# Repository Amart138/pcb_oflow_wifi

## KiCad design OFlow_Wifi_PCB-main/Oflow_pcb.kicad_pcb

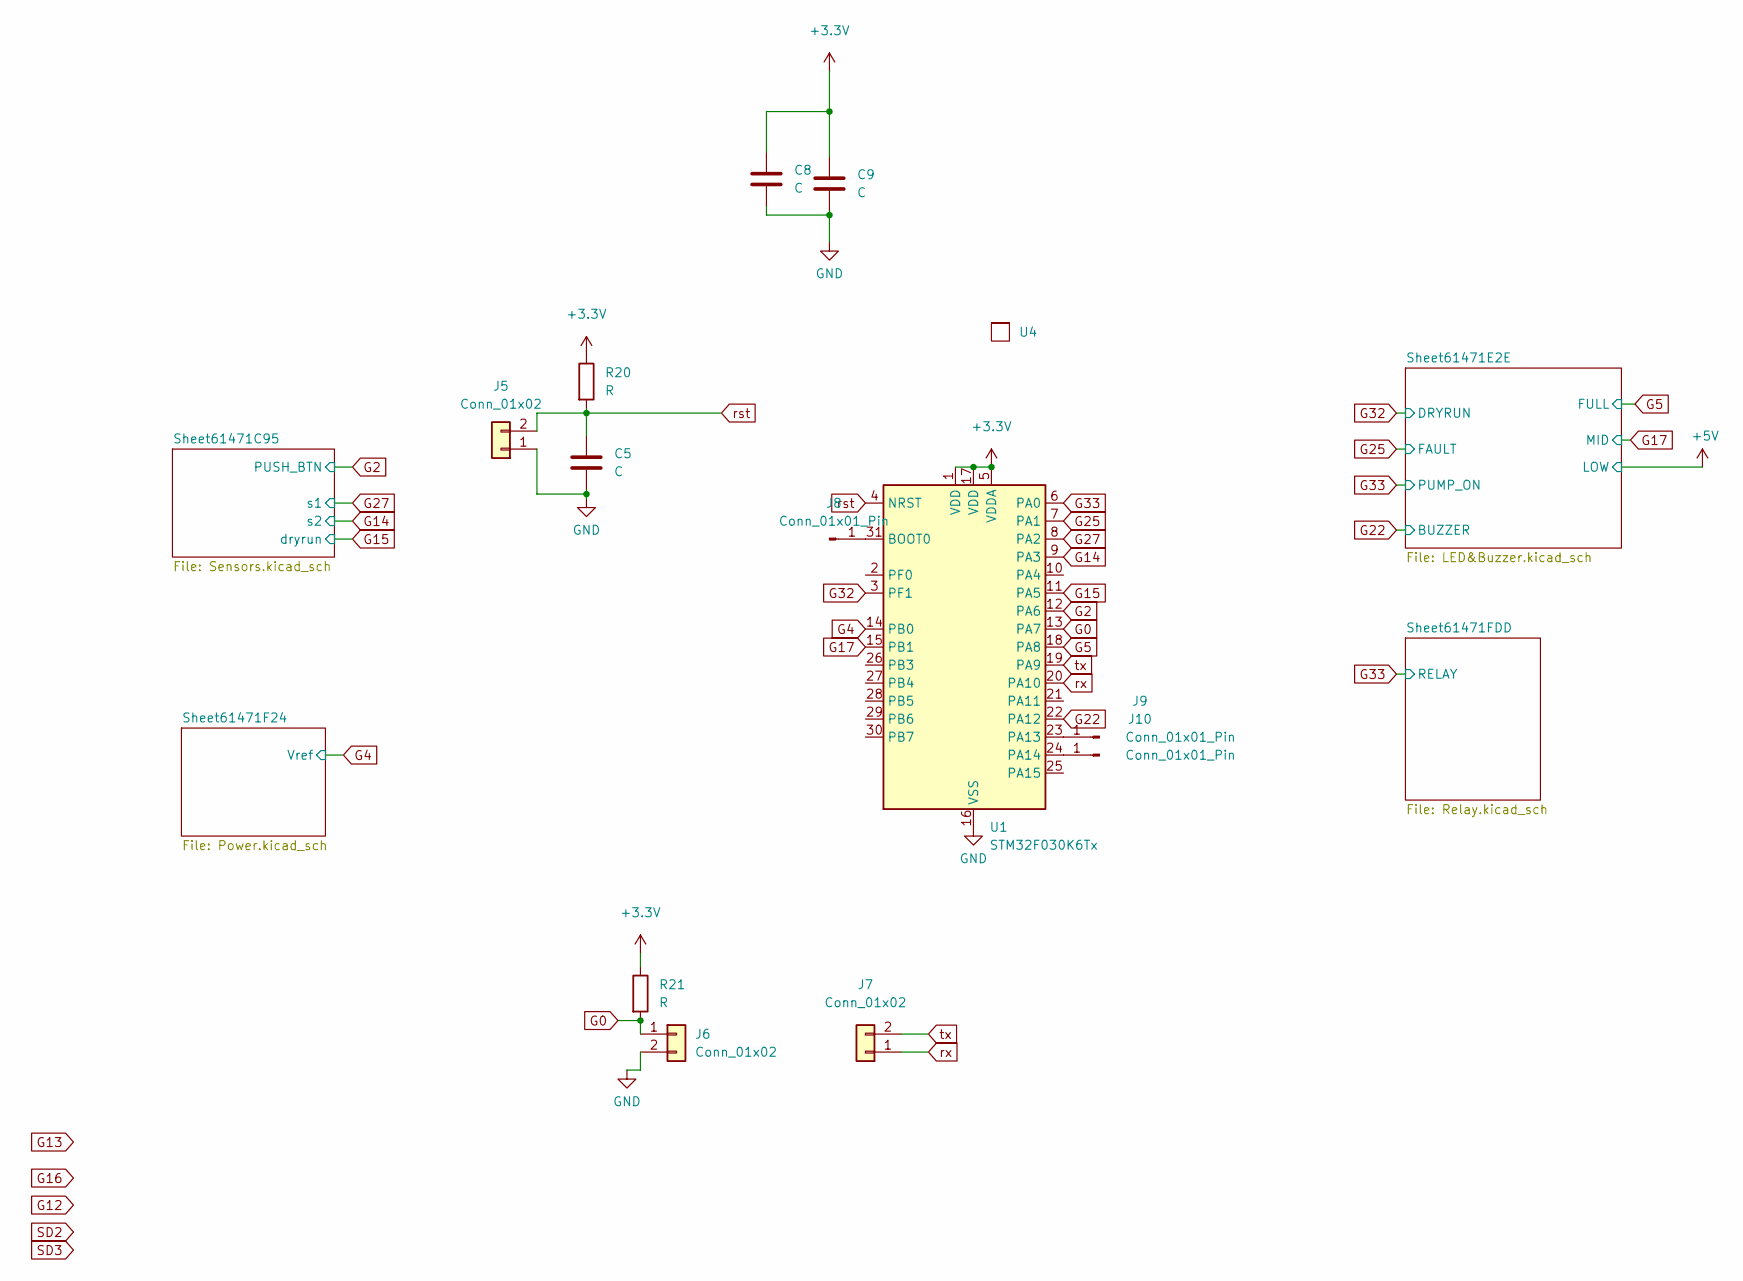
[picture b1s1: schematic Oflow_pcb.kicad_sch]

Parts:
C5, C8, C9: C; CP_Radial_D5.0mm_P2.50mm
J5, J6, J7: Conn_01x02; PinHeader_1x02_P2.54mm_Vertical
J8, J9, J10: Conn_01x01_Pin; PinHeader_1x01_P2.54mm_Vertical
R20, R21: R; R_Axial_DIN0207_L6.3mm_D2.5mm_P10.16mm_Horizontal
U1: STM32F030K6Tx; LQFP-32_7x7mm_P0.8mm
U4: a7670c gsm

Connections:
+3V3: C8.1, C9.1, R20.1, R21.1, U1.1 (VDD), U1.5 (VDDA), U1.17 (VDD); also elsewhere on the board
G0: J6.1, R21.2, U1.13 (PA7)
G2: U1.12 (PA6); also elsewhere on the board
G4: U1.14 (PB0); also elsewhere on the board
G5: U1.18 (PA8); also elsewhere on the board
G14: U1.9 (PA3); also elsewhere on the board
G15: U1.11 (PA5); also elsewhere on the board
G17: U1.15 (PB1); also elsewhere on the board
G22: U1.22 (PA12); also elsewhere on the board
G25: U1.7 (PA1); also elsewhere on the board
G27: U1.8 (PA2); also elsewhere on the board
G32: U1.3 (PF1); also elsewhere on the board
G33: U1.6 (PA0); also elsewhere on the board
GND: C5.2, C8.2, C9.2, J5.1, J6.2, U1.16 (VSS), U1.32 (VSS); also elsewhere on the board
unnamed: J8.1, U1.31 (BOOT0)
unnamed: J9.1, U1.23 (PA13)
unnamed: J10.1, U1.24 (PA14)
rst: C5.1, J5.2, R20.2, U1.4 (NRST)
rx: J7.1, U1.20 (PA10)
tx: J7.2, U1.19 (PA9)

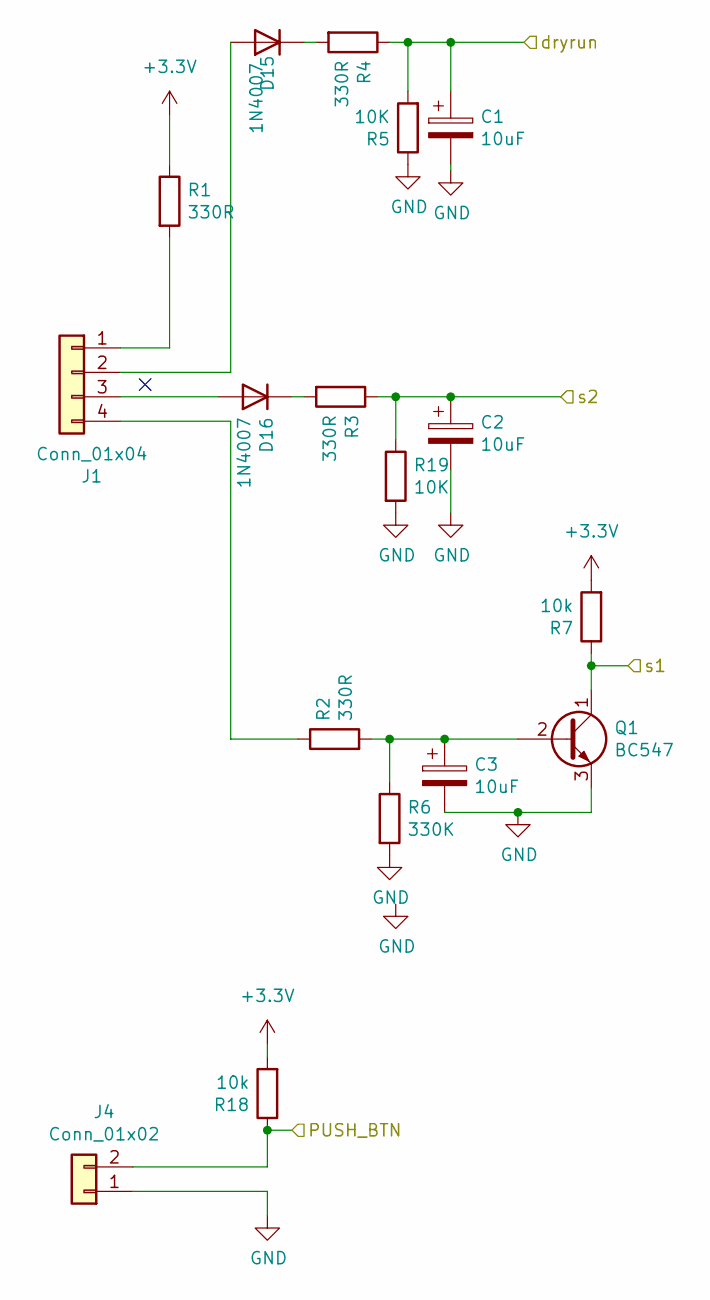
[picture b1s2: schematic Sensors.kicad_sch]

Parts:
C1, C2, C3: 10uF; CP_Radial_D5.0mm_P2.50mm
D15, D16: 1N4007; D_DO-41_SOD81_P10.16mm_Horizontal
J1: Conn_01x04; TerminalBlock_bornier-4_P5.08mm
J4: Conn_01x02; TerminalBlock_bornier-2_P5.08mm
Q1: BC547; TO-92_Inline_Wide
R1, R2, R3, R4: 330R; R_Axial_DIN0207_L6.3mm_D2.5mm_P10.16mm_Horizontal
R5, R19: 10K; R_Axial_DIN0207_L6.3mm_D2.5mm_P10.16mm_Horizontal
R6: 330K; R_Axial_DIN0207_L6.3mm_D2.5mm_P10.16mm_Horizontal
R7: 10k; R_Axial_DIN0207_L6.3mm_D2.5mm_P10.16mm_Horizontal
R18: 10k; R_Axial_DIN0207_L6.3mm_D2.5mm_P5.08mm_Vertical

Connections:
+3V3: R1.1, R7.2, R18.2; also elsewhere on the board
G2: J4.2, R18.1; also elsewhere on the board
G14: C2.1, R3.1, R19.1; also elsewhere on the board
G15: C1.1, R4.1, R5.2; also elsewhere on the board
G27: Q1.1 (C), R7.1; also elsewhere on the board
GND: C1.2, C2.2, C3.2, J4.1, Q1.3 (E), R5.1, R6.2, R19.2; also elsewhere on the board
unnamed: D15.2 (A), J1.2
unnamed: D15.1 (K), R4.2
unnamed: D16.2 (A), J1.3
unnamed: D16.1 (K), R3.2
unnamed: J1.1, R1.2
unnamed: J1.4, R2.1
unnamed: C3.1, Q1.2 (B), R2.2, R6.1

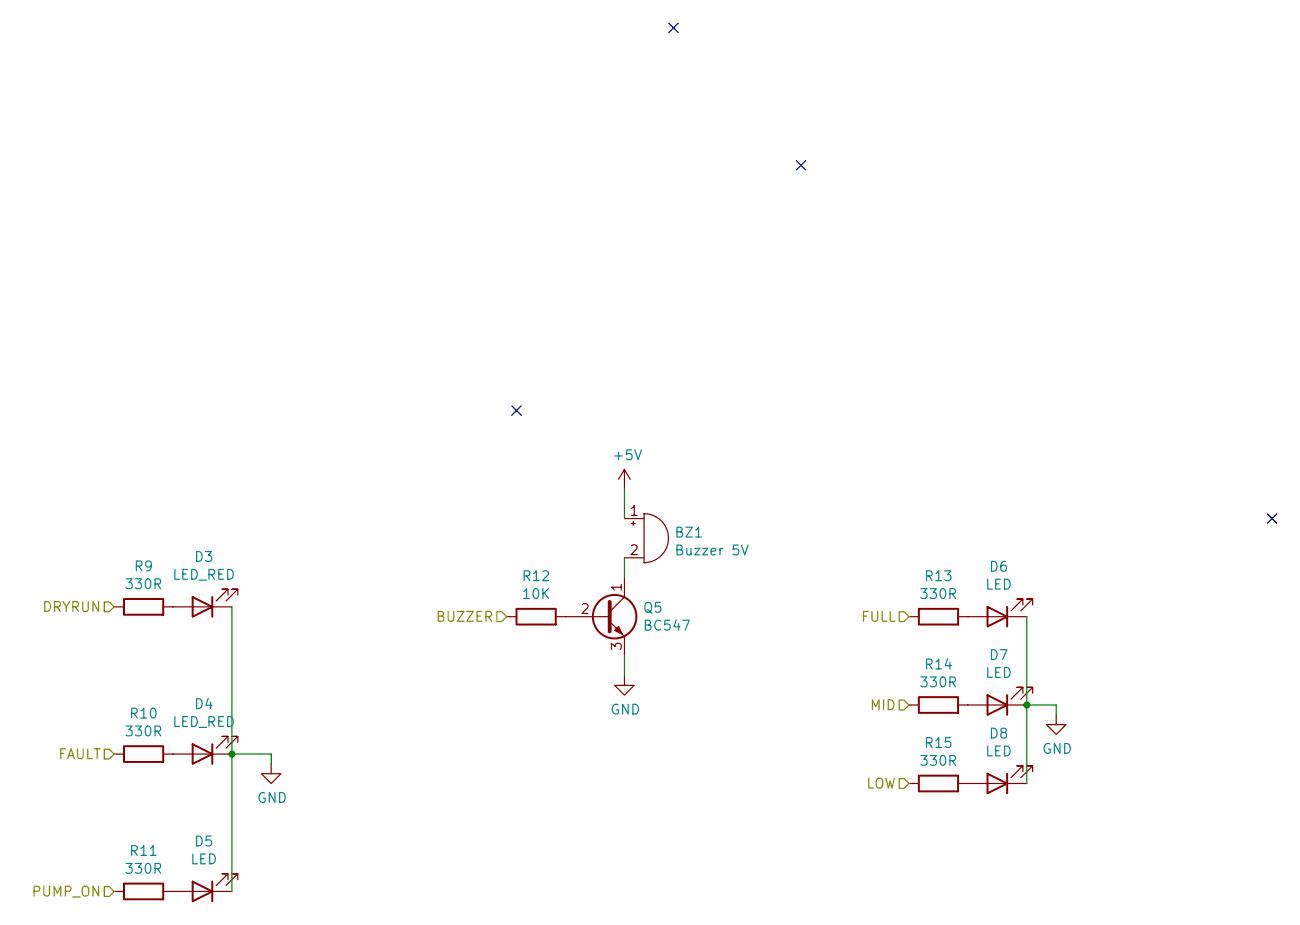
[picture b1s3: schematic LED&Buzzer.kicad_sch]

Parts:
BZ1: Buzzer 5V; Buzzer_12x9.5RM7.6
D3, D4: LED_RED; LED_D5.0mm_Clear
D5, D6, D7, D8: LED; LED_D5.0mm_Clear
Q5: BC547; TO-92_Inline_Wide
R9, R10, R11, R13, R14, R15: 330R; R_Axial_DIN0207_L6.3mm_D2.5mm_P10.16mm_Horizontal
R12: 10K; R_Axial_DIN0207_L6.3mm_D2.5mm_P5.08mm_Vertical

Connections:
+5V: BZ1.1 (-), R15.1; also elsewhere on the board
G5: R13.1; also elsewhere on the board
G17: R14.1; also elsewhere on the board
G22: R12.1; also elsewhere on the board
G25: R10.1; also elsewhere on the board
G32: R9.1; also elsewhere on the board
G33: R11.1; also elsewhere on the board
GND: D3.1 (K), D4.1 (K), D5.1 (K), D6.1 (K), D7.1 (K), D8.1 (K), Q5.3 (E); also elsewhere on the board
unnamed: BZ1.2 (+), Q5.1 (C)
unnamed: D3.2 (A), R9.2
unnamed: D4.2 (A), R10.2
unnamed: D5.2 (A), R11.2
unnamed: D6.2 (A), R13.2
unnamed: D7.2 (A), R14.2
unnamed: D8.2 (A), R15.2
unnamed: Q5.2 (B), R12.2

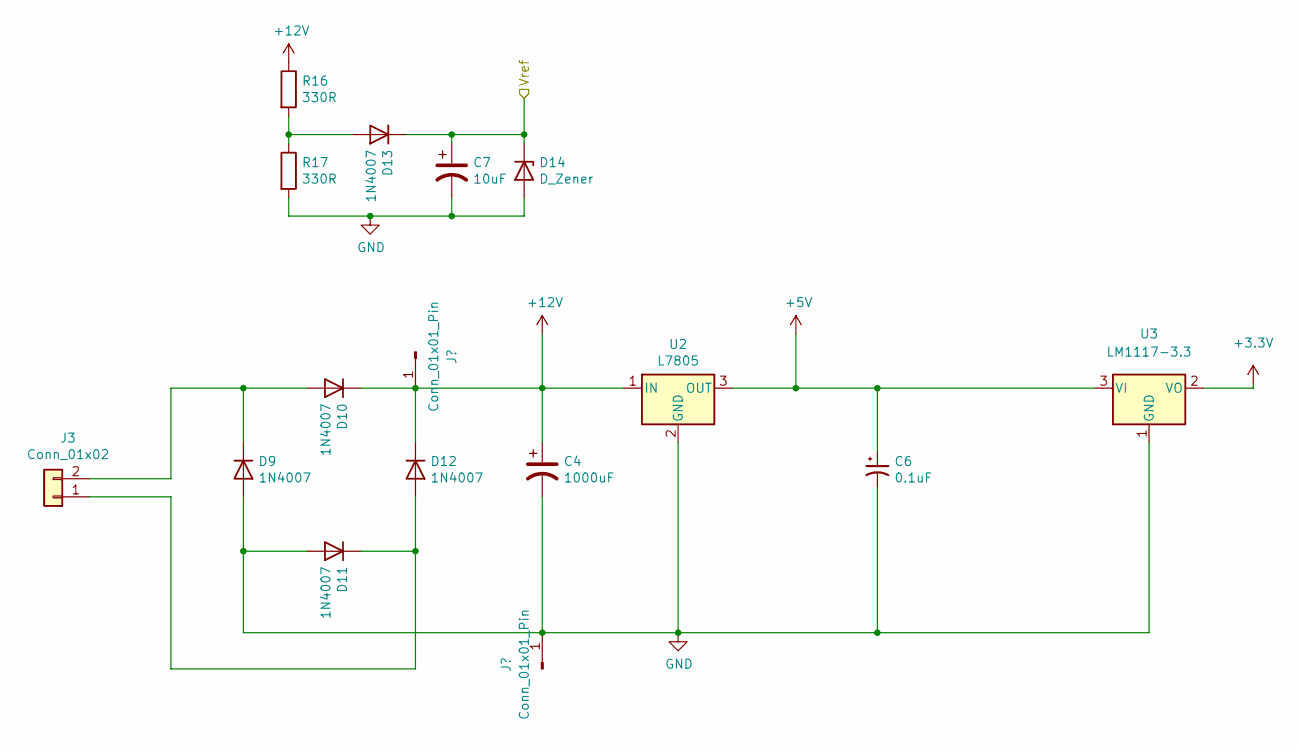
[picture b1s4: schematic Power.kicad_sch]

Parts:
C4: 1000uF; CP_Radial_D10.0mm_P5.00mm
C6: 0.1uF; CP_Radial_D5.0mm_P2.50mm
C7: 10uF; CP_Radial_D5.0mm_P2.50mm
D9, D10, D11, D12, D13: 1N4007; D_DO-41_SOD81_P10.16mm_Horizontal
D14: D_Zener; D_DO-41_SOD81_P5.08mm_Vertical_KathodeUp
J3: Conn_01x02; TerminalBlock_bornier-2_P5.08mm
J11, J12: Conn_01x01_Pin; PinHeader_1x01_P2.54mm_Vertical
R16, R17: 330R; R_Axial_DIN0207_L6.3mm_D2.5mm_P10.16mm_Horizontal
U2: L7805; TO-220-3_Vertical
U3: LM1117-3.3; SOT-223-3_TabPin2

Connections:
+3V3: U3.2 (VO); also elsewhere on the board
+5V: C6.1, U2.3 (OUT), U3.3 (VI); also elsewhere on the board
+12V: C4.1, D10.1 (K), D12.1 (K), J11.1, R16.1, U2.1 (IN); also elsewhere on the board
G4: C7.1, D13.1 (K), D14.1 (K); also elsewhere on the board
GND: C4.2, C6.2, C7.2, D9.2 (A), D11.2 (A), D14.2 (A), J12.1, R17.2, U2.2 (GND), U3.1 (GND); also elsewhere on the board
unnamed: D9.1 (K), D10.2 (A), J3.2
unnamed: D11.1 (K), D12.2 (A), J3.1
unnamed: D13.2 (A), R16.2, R17.1

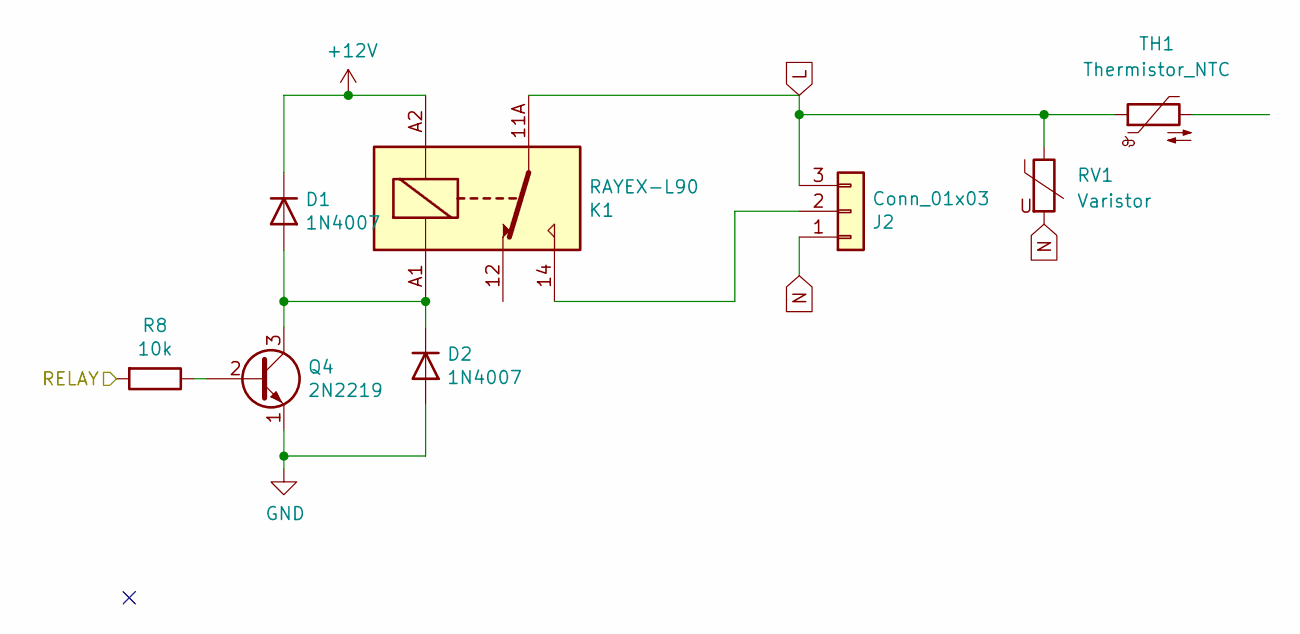
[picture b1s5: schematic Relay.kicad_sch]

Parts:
D1, D2: 1N4007; D_DO-41_SOD81_P10.16mm_Horizontal
J2: Conn_01x03; TerminalBlock_MetzConnect_Type175_RT02703HBLC_1x03_P7.50mm_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
K1: RAYEX-L90; Relay_SPDT_RAYEX-L90
Q4: 2N2219; TO-92_Inline_Wide
R8: 10k; R_Axial_DIN0207_L6.3mm_D2.5mm_P10.16mm_Horizontal
RV1: Varistor; R_Axial_DIN0411_L9.9mm_D3.6mm_P20.32mm_Horizontal
TH1: Thermistor_NTC; R_Axial_DIN0411_L9.9mm_D3.6mm_P7.62mm_Vertical

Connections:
+12V: D1.1 (K), K1.A2; also elsewhere on the board
G33: R8.2; also elsewhere on the board
GND: D2.2 (A), Q4.1 (E); also elsewhere on the board
L: J2.3, K1.11A, K1.11B, RV1.1, TH1.1
N: J2.1, RV1.2
unnamed: D1.2 (A), D2.1 (K), K1.A1, Q4.3 (C)
unnamed: J2.2, K1.14
unnamed: Q4.2 (B), R8.1

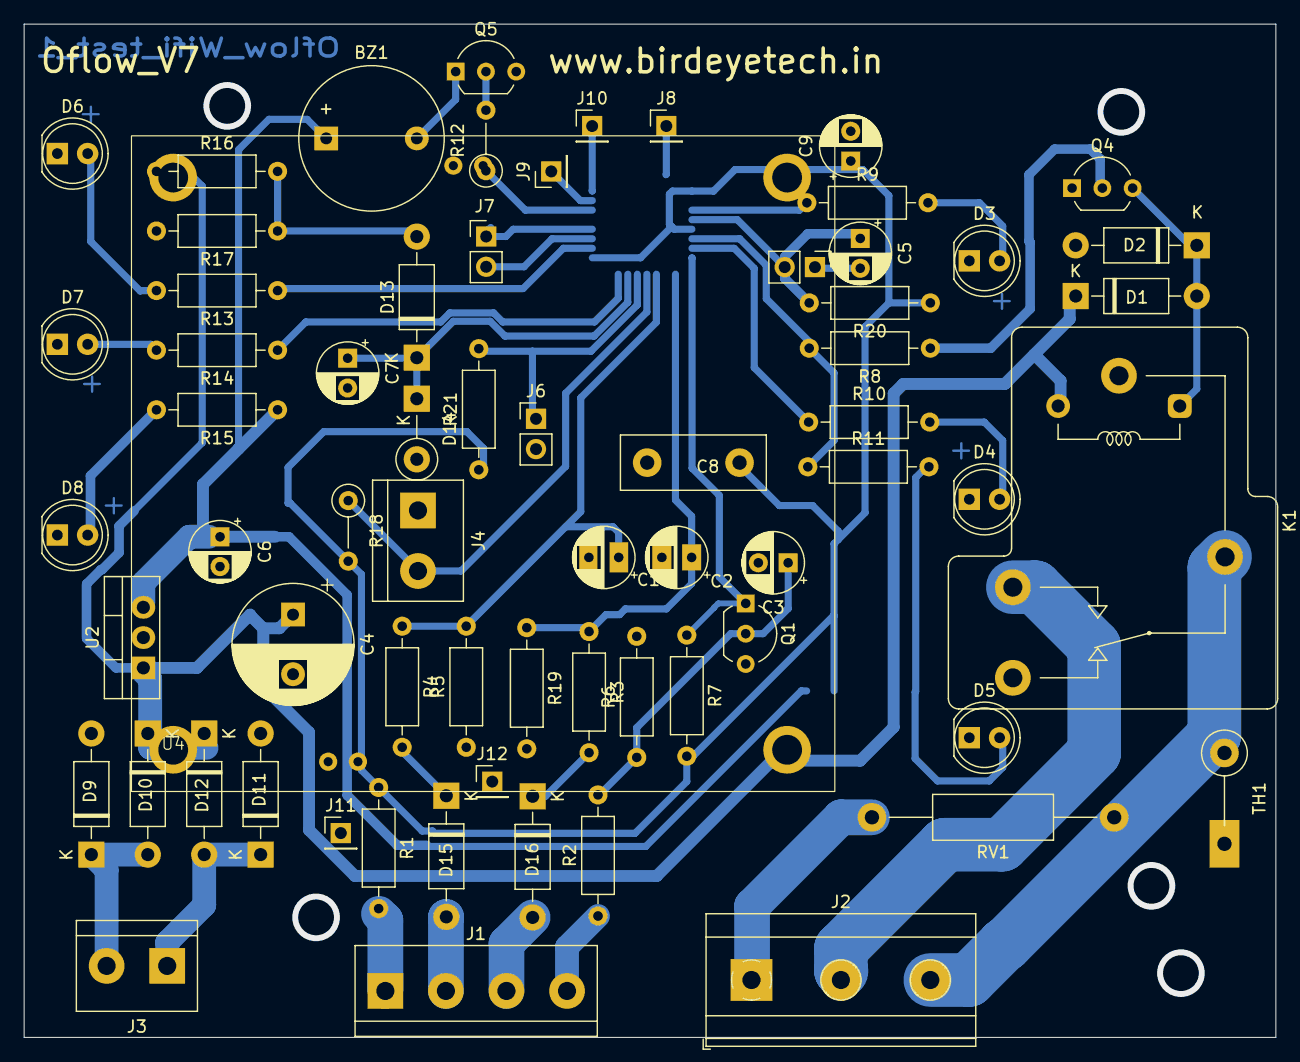
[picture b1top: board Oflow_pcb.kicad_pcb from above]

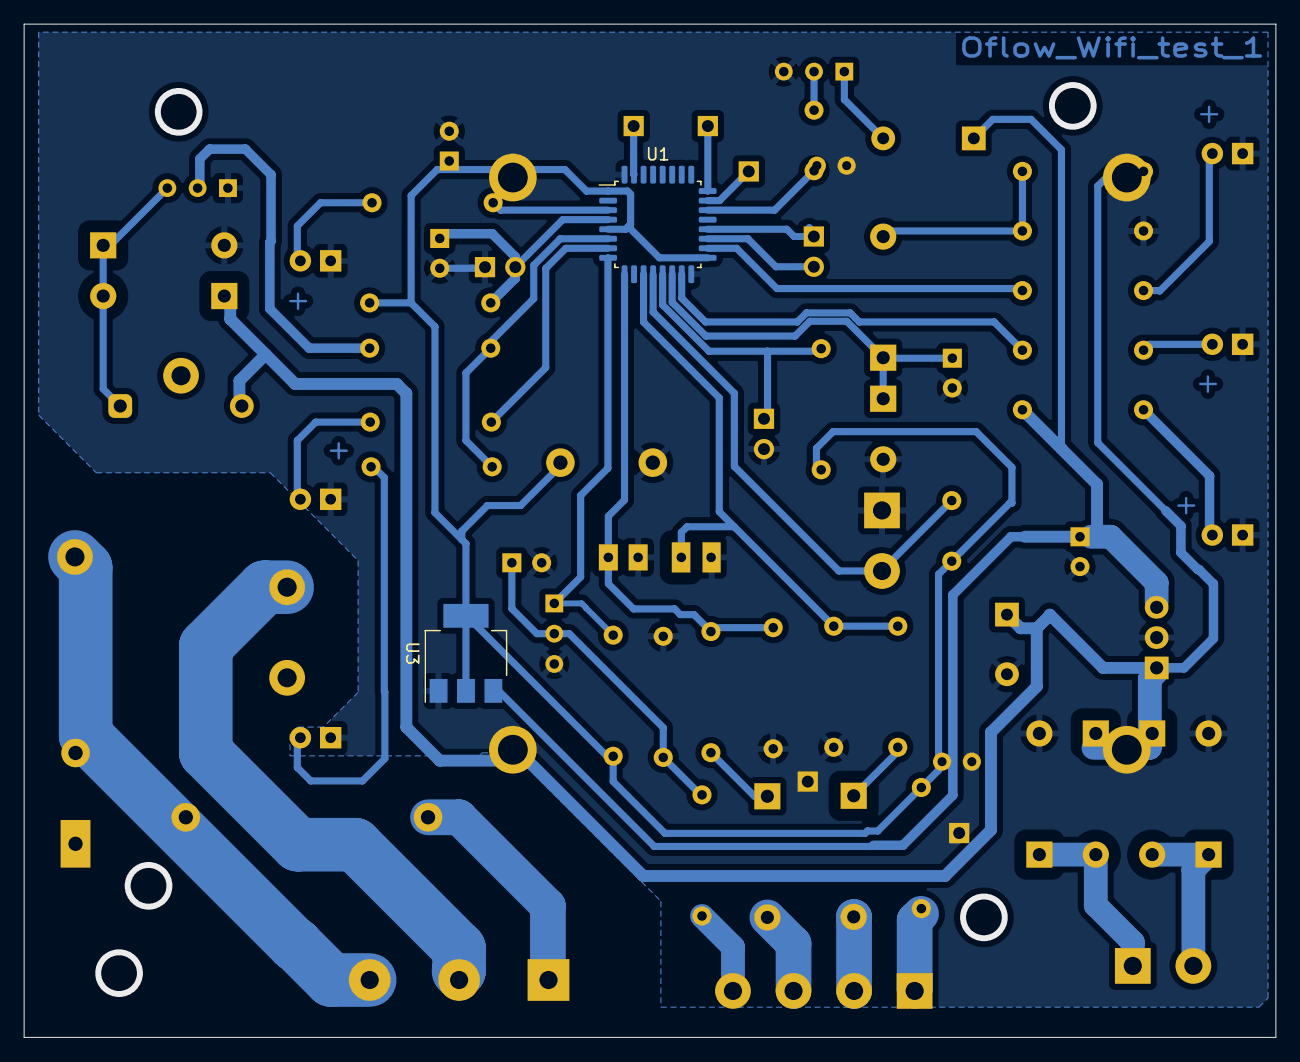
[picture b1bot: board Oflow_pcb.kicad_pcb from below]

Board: 2 copper layers, 105.0 x 85.0 mm, 69 parts (2 on the bottom side), 45 nets.
